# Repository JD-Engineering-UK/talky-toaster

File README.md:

# Talky-toaster

Inspired by the television show Red Dwarf.

This repository contains the firmware for a real-life version of the talky-toaster using a mmWave presence sensor, an audio amplifier and an ESP32S3 microcontroller.

## Features
- OTA update
- Time aware (NTP sync over WiFi)
- MP3 decompression and playback
- Motion sensor reading (including distance)

## TODO:
- [ ] Telemetry
- [ ] Configuration
- [ ] Silent OTA Update (Boot sounds play after OTA update but I don't want sounds playing out of hours)

## Possible Future Development:
- [ ] LED lights when the toaster is "speaking"
- [ ] Integrate more closely with a toaster. Possibly to detect how well-done the toast is or perhaps to simply have a voice line when the toaster lever is pressed down.
- [ ] Implement "wake word detection" to detect rejections of the toasters offers of grilled bread products and respond accordingly

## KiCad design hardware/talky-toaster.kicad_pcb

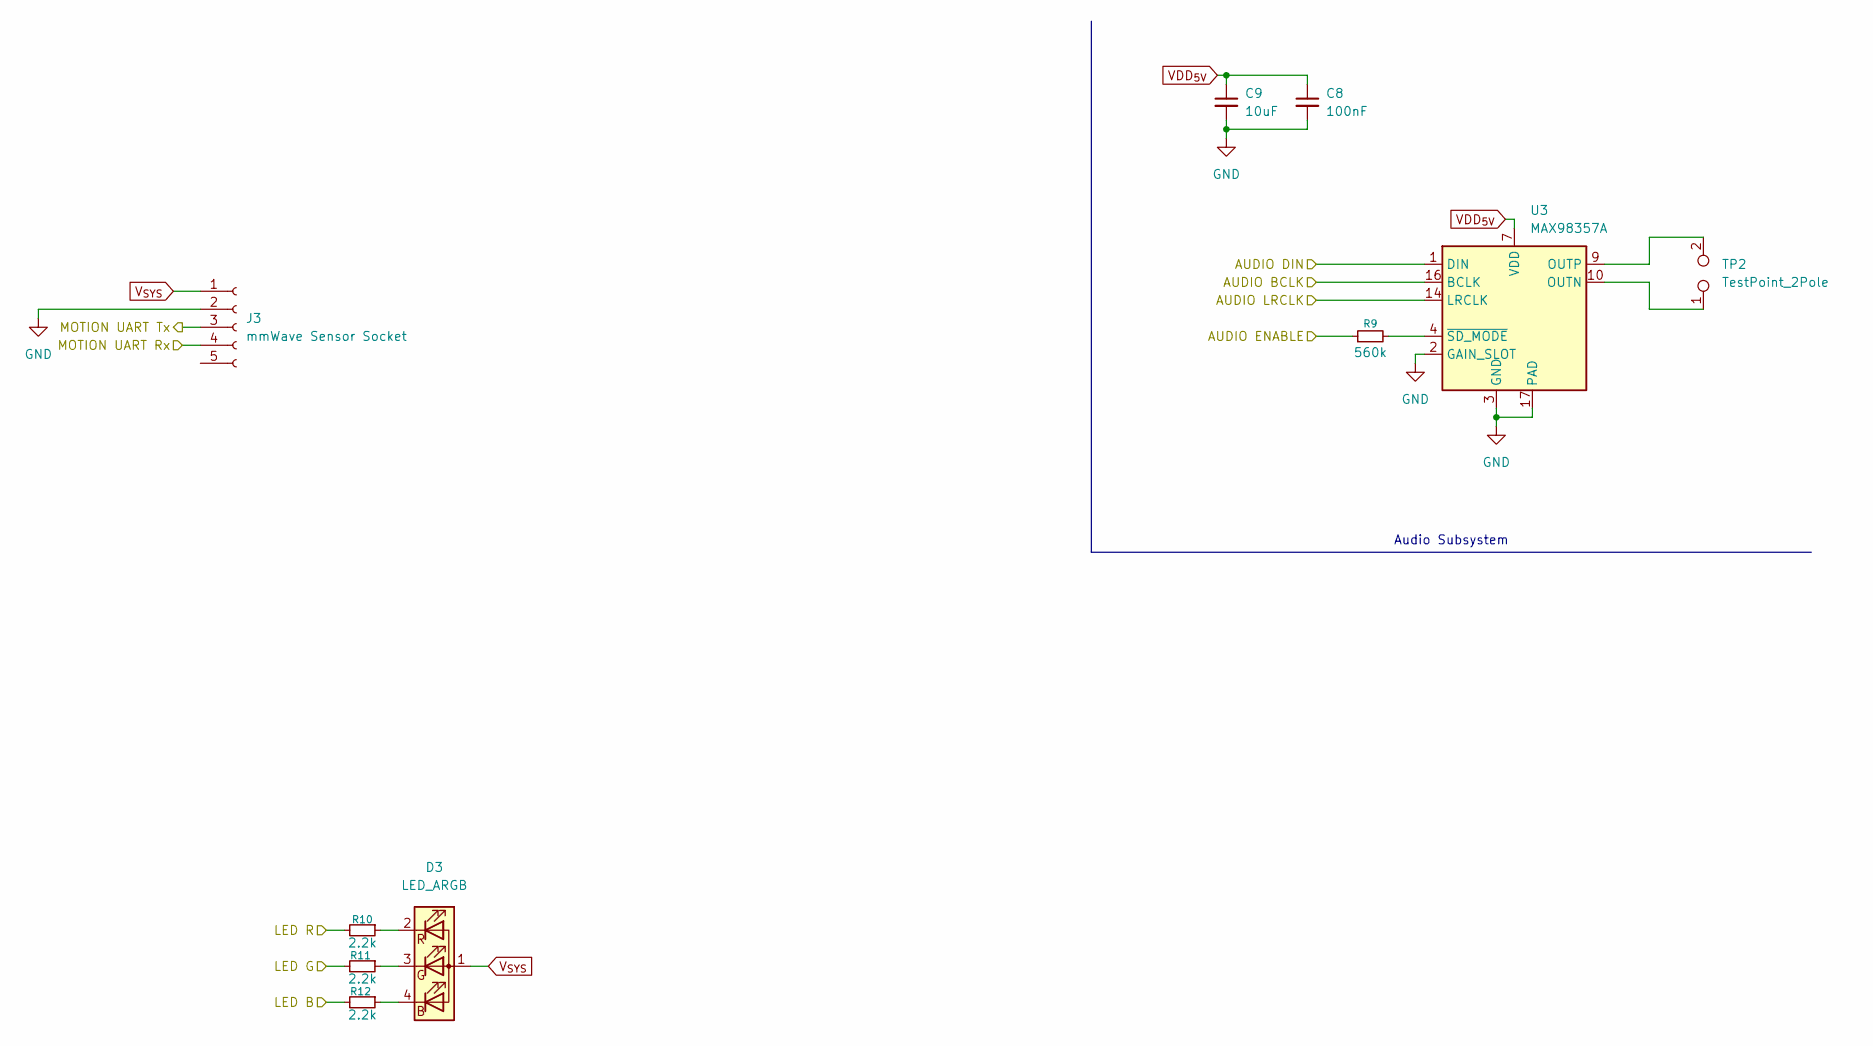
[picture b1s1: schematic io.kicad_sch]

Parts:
C8: 100nF; C_0402_1005Metric_Pad0.74x0.62mm_HandSolder
C9: 10uF; C_0603_1608Metric_Pad1.08x0.95mm_HandSolder
D3: LED_ARGB; 19237R6GHBHCA012T
J3: mmWave Sensor Socket; PinSocket_1x05_P2.54mm_Vertical
R9: 560k; R_0402_1005Metric_Pad0.72x0.64mm_HandSolder
R10, R11, R12: 2.2k; R_0402_1005Metric_Pad0.72x0.64mm_HandSolder
TP2: TestPoint_2Pole; PinSocket_2x01_P2.54mm_Vertical
U3: MAX98357A; TQFN-16-1EP_3x3mm_P0.5mm_EP1.23x1.23mm_ThermalVias

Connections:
/IO/AUDIO BCLK: U3.16 (BCLK); also elsewhere on the board
/IO/AUDIO DIN: U3.1 (DIN); also elsewhere on the board
/IO/AUDIO ENABLE: R9.1; also elsewhere on the board
/IO/AUDIO LRCLK: U3.14 (LRCLK); also elsewhere on the board
/IO/LED B: R12.2; also elsewhere on the board
/IO/LED G: R11.2; also elsewhere on the board
/IO/LED R: R10.2; also elsewhere on the board
/IO/MOTION UART Rx: J3.4; also elsewhere on the board
/IO/MOTION UART Tx: J3.3; also elsewhere on the board
GND: C8.2, C9.2, J3.2, U3.2 (GAIN_SLOT), U3.3 (GND), U3.11 (GND), U3.15 (GND), U3.17 (PAD); also elsewhere on the board
unnamed: D3.4 (BK), R12.1
unnamed: D3.3 (GK), R11.1
unnamed: D3.2 (RK), R10.1
unnamed: TP2.1, U3.10 (OUTN)
unnamed: TP2.2, U3.9 (OUTP)
unnamed: R9.2, U3.4 (~SD_MODE)
VDD_{5V}: C8.1, C9.1, U3.7 (VDD), U3.8 (VDD); also elsewhere on the board
V_{SYS}: D3.1 (A), J3.1; also elsewhere on the board

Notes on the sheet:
Audio Subsystem

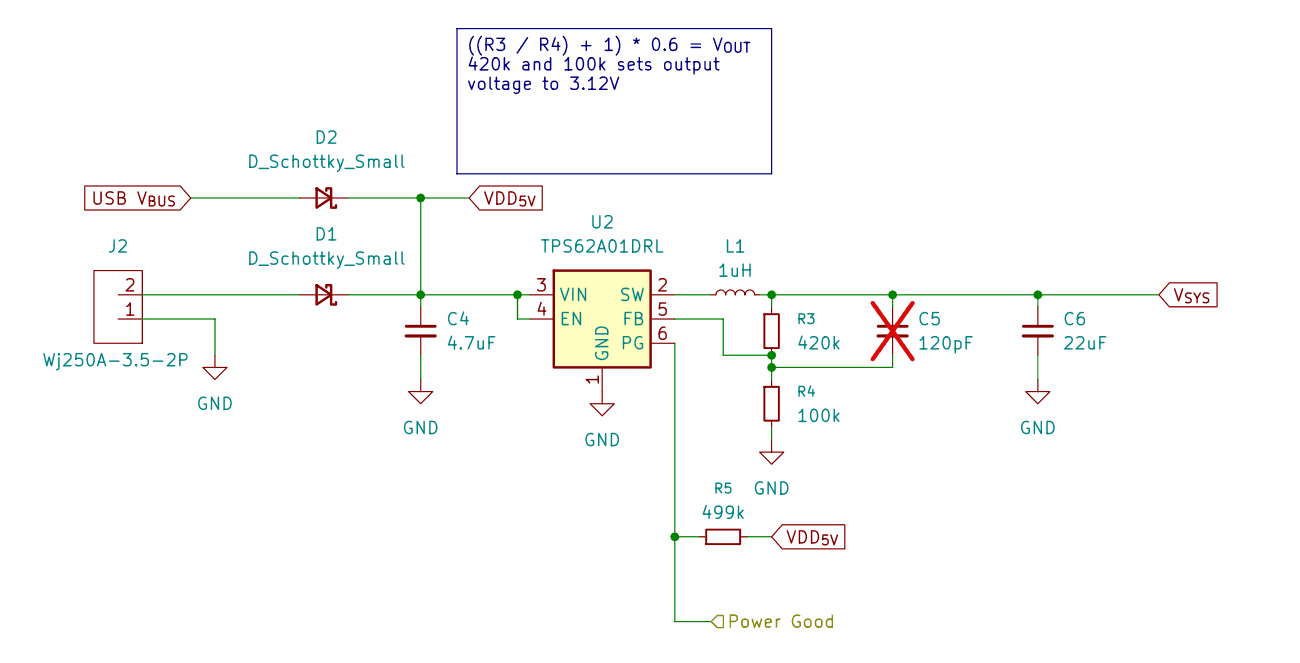
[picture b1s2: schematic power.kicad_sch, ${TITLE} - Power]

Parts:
C4: 4.7uF; C_0603_1608Metric_Pad1.08x0.95mm_HandSolder
C5: 120pF; C_0402_1005Metric_Pad0.74x0.62mm_HandSolder; not fitted
C6: 22uF; C_0603_1608Metric_Pad1.08x0.95mm_HandSolder
D1, D2: D_Schottky_Small; D_SOD-123
J2: Wj250A-3.5-2P; Spring Terminal 2P
L1: 1uH; L_1812_4532Metric_Pad1.30x3.40mm_HandSolder
R3: 420k; R_0402_1005Metric_Pad0.72x0.64mm_HandSolder
R4: 100k; R_0402_1005Metric_Pad0.72x0.64mm_HandSolder
R5: 499k; R_0402_1005Metric_Pad0.72x0.64mm_HandSolder
U2: TPS62A01DRL; SOT-563

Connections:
/MCU/Power Good: R5.1, U2.6 (PG); also elsewhere on the board
GND: C4.2, C6.2, J2.1, R4.2, U2.1 (GND); also elsewhere on the board
unnamed: D1.2 (A), J2.2
unnamed: C5.2, R3.2, R4.1, U2.5 (FB)
unnamed: L1.1, U2.2 (SW)
USB V_{BUS}: D2.2 (A); also elsewhere on the board
VDD_{5V}: C4.1, D1.1 (K), D2.1 (K), R5.2, U2.3 (VIN), U2.4 (EN); also elsewhere on the board
V_{SYS}: C5.1, C6.1, L1.2, R3.1; also elsewhere on the board

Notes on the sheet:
((R3 / R4) + 1) * 0.6 = V_{OUT} 420k and 100k sets output voltage to 3.12V

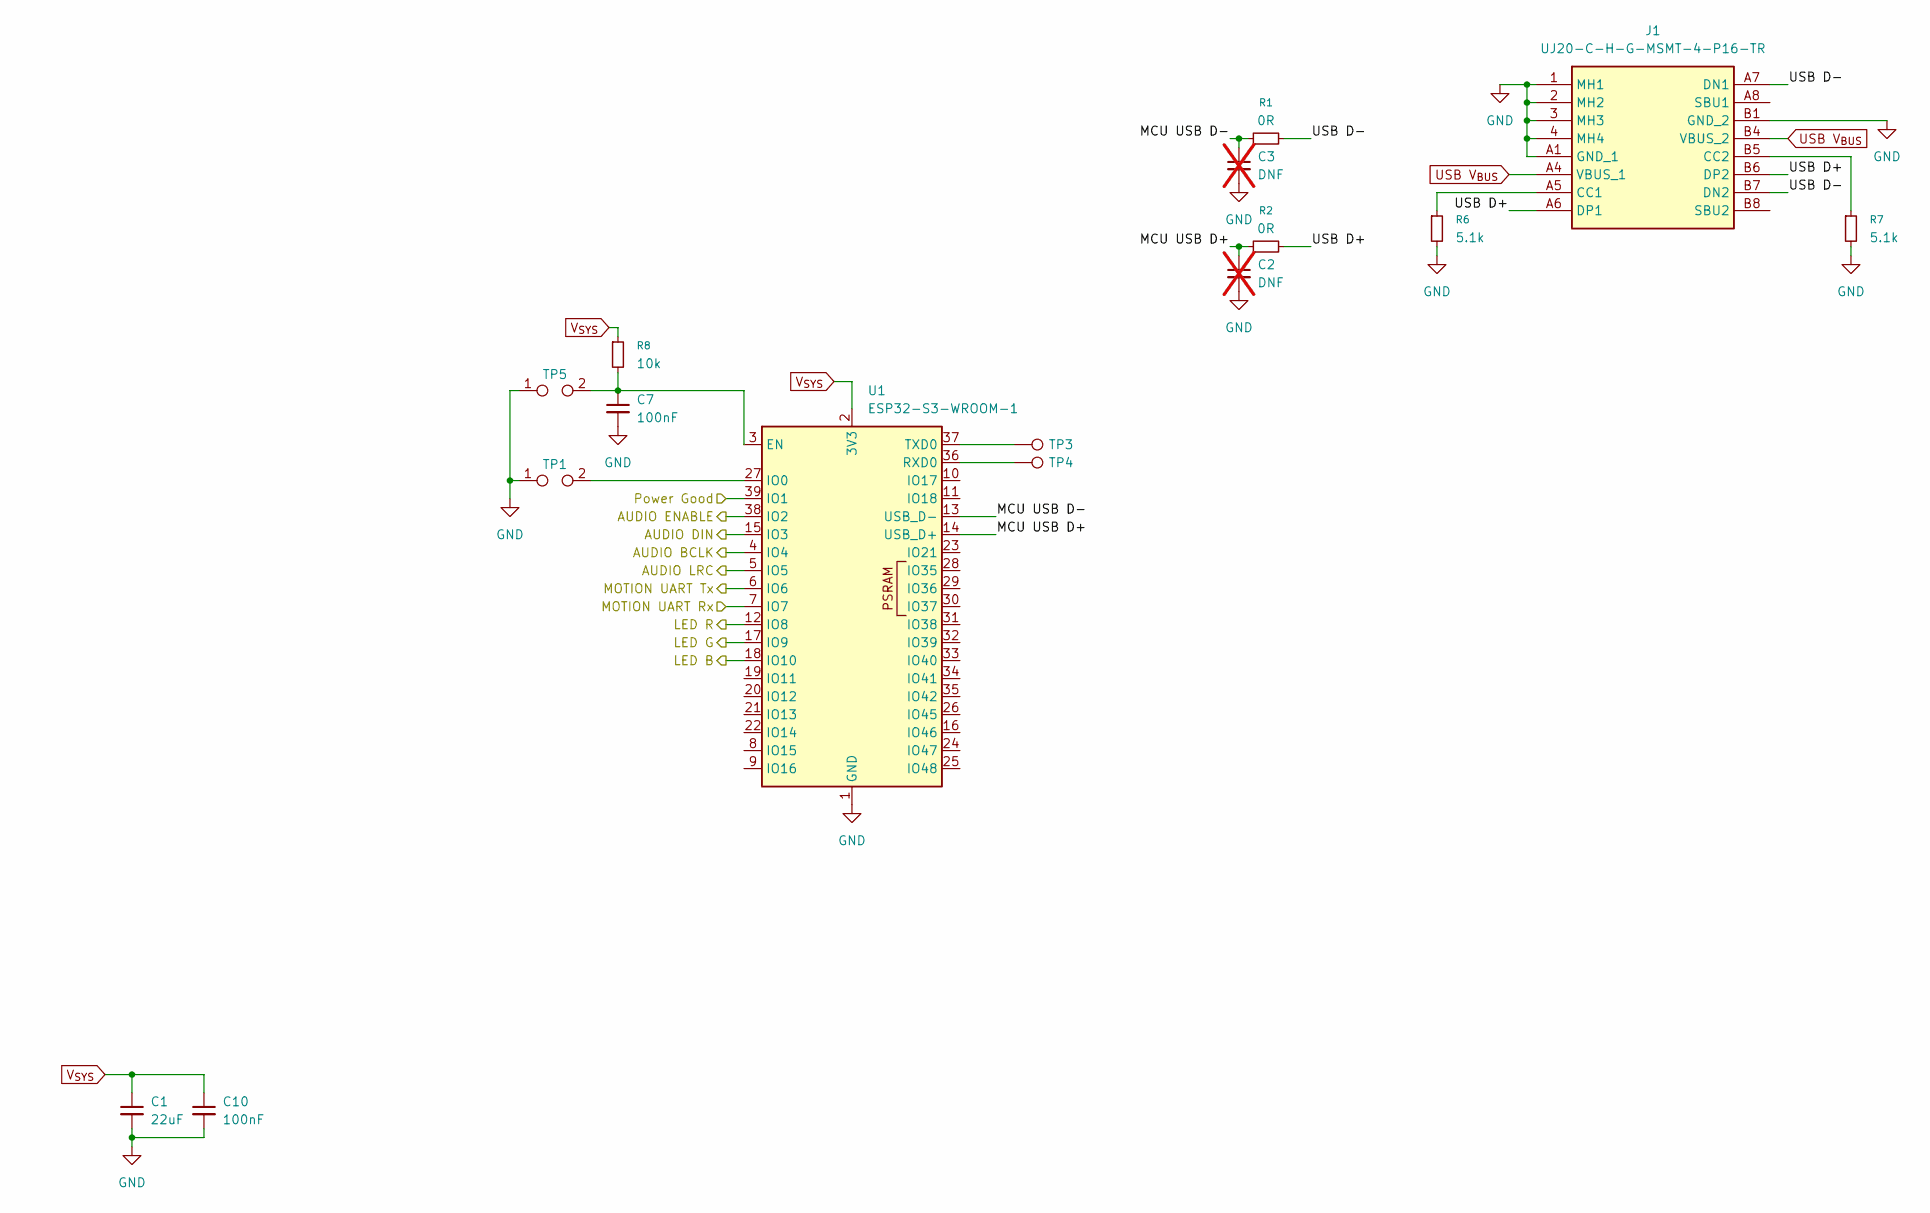
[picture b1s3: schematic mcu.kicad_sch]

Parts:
C1: 22uF; C_0603_1608Metric_Pad1.08x0.95mm_HandSolder
C2, C3: DNF; C_0402_1005Metric_Pad0.74x0.62mm_HandSolder; not fitted
C7, C10: 100nF; C_0402_1005Metric_Pad0.74x0.62mm_HandSolder
J1: UJ20-C-H-G-MSMT-4-P16-TR; UJ20CHGMSMT4P16TR; Mouser Part Number 179-UJ20CHGMSMT4P16T
R1, R2: 0R; R_0402_1005Metric_Pad0.72x0.64mm_HandSolder
R6, R7: 5.1k; R_0402_1005Metric_Pad0.72x0.64mm_HandSolder
R8: 10k; R_0402_1005Metric_Pad0.72x0.64mm_HandSolder
TP1, TP5: TestPoint_2Pole; PinHeader_2x01_P1.00mm_Vertical_SMD
TP3, TP4: TestPoint; TestPoint_Pad_D1.0mm
U1: ESP32-S3-WROOM-1

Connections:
/IO/AUDIO BCLK: U1.4 (IO4); also elsewhere on the board
/IO/AUDIO DIN: U1.15 (IO3); also elsewhere on the board
/IO/AUDIO ENABLE: U1.38 (IO2); also elsewhere on the board
/IO/AUDIO LRCLK: U1.5 (IO5); also elsewhere on the board
/IO/LED B: U1.18 (IO10); also elsewhere on the board
/IO/LED G: U1.17 (IO9); also elsewhere on the board
/IO/LED R: U1.12 (IO8); also elsewhere on the board
/IO/MOTION UART Rx: U1.6 (IO6); also elsewhere on the board
/IO/MOTION UART Tx: U1.7 (IO7); also elsewhere on the board
/MCU/MCU USB D+: C2.1, R2.1, U1.14 (USB_D+)
/MCU/MCU USB D-: C3.1, R1.1, U1.13 (USB_D-)
/MCU/Power Good: U1.39 (IO1); also elsewhere on the board
/MCU/USB D+: J1.A6 (DP1), J1.B6 (DP2), R2.2
/MCU/USB D-: J1.A7 (DN1), J1.B7 (DN2), R1.2
GND: C1.2, C2.2, C3.2, C7.2, C10.2, J1.1 (MH1), J1.2 (MH2), J1.3 (MH3), J1.4 (MH4), J1.A1 (GND_1), J1.B1 (GND_2), R6.2, R7.2, TP1.1, TP5.1, U1.1 (GND), U1.40 (GND), U1.41 (GND); also elsewhere on the board
unnamed: J1.A5 (CC1), R6.1
unnamed: J1.B5 (CC2), R7.1
unnamed: C7.1, R8.2, TP5.2, U1.3 (EN)
unnamed: TP1.2, U1.27 (IO0)
unnamed: TP4.1, U1.36 (RXD0)
unnamed: TP3.1, U1.37 (TXD0)
USB V_{BUS}: J1.A4 (VBUS_1), J1.B4 (VBUS_2); also elsewhere on the board
V_{SYS}: C1.1, C10.1, R8.1, U1.2 (3V3); also elsewhere on the board

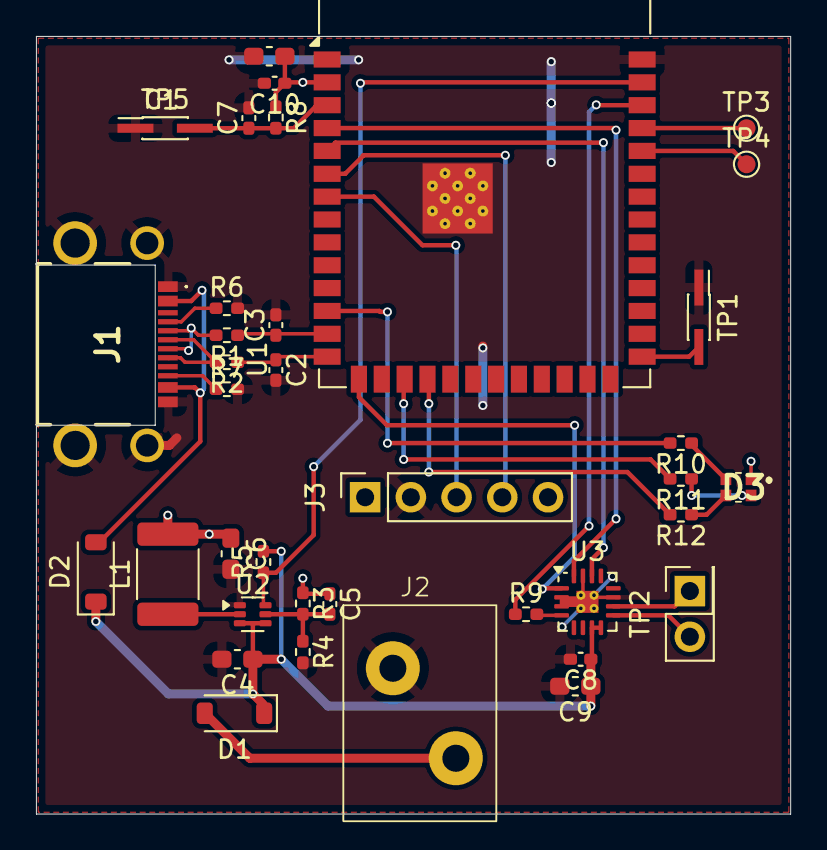
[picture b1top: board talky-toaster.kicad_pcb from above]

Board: 2 copper layers, 41.9 x 43.2 mm, 37 parts (0 on the bottom side), 33 nets.

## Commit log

2025-02-08 Update readme Found out how to configure the sensor
2025-02-09 High pitched sound output. About to try adding playback from file.
2025-02-09 Audio playing!
2025-02-09 Add introduction
    New problem: run out of flash memory...
2025-02-09 Adding ESP-ADF to the project
2025-02-14 Adding ESP-ADF
2025-02-21 Trim down size to get it building again
2025-02-21 Set the project name...
2025-02-21 Update config defaults from example.
2025-02-22 Playing MP3 files
2025-02-22 Dev board I'm using has 8MB of additional RAM that wasn't enabled
2025-02-22 Simplified using embedded audio files and queueing them for playback
2025-04-07 WiFi
2025-05-17 WiFi Working with SNTP. Boot audio bugs out
2025-05-25 Surviving design files...
    I messed up git and fork. Most of the files are gone. This is what I could recover.
2026-02-15 New WiFi component. Enable motion sensor handling. Play audio when motion detected.
2026-03-06 Logic refactor and tweaking
2026-04-30 Beginning of FOTA
2026-04-30 First FOTA supported version
2026-04-30 Return time limits to normal
